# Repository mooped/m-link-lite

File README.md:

# M-Link Lite

M-Link Lite is a receiver for combat robotics based on the ESP8266 microcontroller. It acts as a WiFi access point and can be controlled from a WebSocket.

M-Link Lite hosts a web server with a basic page for controlling a simple combat robot.

Additional files can be uploaded to control more complex robots with up to 6 channels.

The servo pulsewidth data sent to the WebSocket is passed straight through to the outputs to avoid limiting possibilities.

M-Link Lite has a configurable failsafe so if no updates are received for 500ms the outputs will be put into a safe state.

When turned on M-Link will create a WiFi Access Point named m-link-XXXXXX where XXXXXX is a unique set of digits that identifies the device. The device should be labelled with this ID. A single user can connect to this access point and the controller page should be accessible by navigating to http://m-link-XXXXXXX.local or if wildcard DNS is enabled to any url e.g. http://m-link/ .

When connected to the access point the device will always be available at http://192.168.4.1 . If you are having trouble when using the access point from a mobile device, turning off mobile internet so WiFi is the only option may help.

Once configured via the access point you can enter details for your own access point and the device will connect to it from then on.

## Extending M-Link Lite

The default Drive page on the M-Link Lite device provides a single virtual joystick that directly drives the first two channels. It performs no mixing and is designed for a dual ESC with onboard mixing.

If you wish to use all 6 channels or other features you can upload additional files through the File Manager page that make use of these features.

As a starting point it is recommended to download the default 'Drive' page from [main/joystick.html](main/joystick.html), modify it. You can use the File Manager page on the device to upload and test the modified version.

The on-screen Joystick is implemented with [jeromeetienne/virtualjoystick.js](https://github.com/jeromeetienne/virtualjoystick.js) which has its own documentation and examples for adding additional joysticks.

Some examples are provided for implementing [one](examples/joystick.html), [two](examples/two_stick.html), or [three](examples/three_stick.html) on-screen joysticks in the [examples folder](examples) of the project.

The page talks to the M-Link Lite by sending JSON messages over a websocket and the device will send JSON messages back in response.

The code at line 40 of the Drive page sends an initial packet to center all outputs, and it also sends a set of failsafe values which will be applied if a packet is not received for 500 milliseconds. This is intended to avoid the robot going out of control if the user closes their browser, turns of the controlling device, or the connection is otherwise disrupted.

```
        ws.onopen = function() {
          ws.send(
            JSON.stringify(
              {
                servos: [
                  1500,
                  1500,
                  1500,
                  1500,
                  1500,
                  1500
                ],
                failsafes: [
                  1500,
                  1500,
                  1500,
                  1500,
                  1500,
                  1500
                ],
                query: "settings"
              }
            )
          );
        };
```

The default failsafes will stop a brushed ESC that has a reverse feature and center a servo. If you intend to build a robot using non-reversible ESCs or your servo driven mechanisms require a different position on failsafe you will need to update these values.

The values sent in the `servos` and `failsafes` array are the pulse width that will be sent to the servo in microseconds. 1000 microseconds is usually fully left, 2000 microseconds is fully right, and 1500 microseconds is centered. You can send 0 microseconds to stop sending a signal, which will cause many servos to idle, but depending on the servos you will need to be careful with other out of range values which may cause unexpected behaviour and/or damage.

For the `failsafes` array a value of -1 can be set instead of a pulsewidth to hold the channel at its last position when in failsafe.

The code between lines 103 and 124 is responsible for sending updated values to the M-Link Lite 30 times a second. By altering the values to the `servos` array you can make use of all 6 channels.

```
      setInterval(function(){
        const x = Math.round(joystick.deltaX() * 5);
        const y = Math.round(joystick.deltaY() * 5);
        $msg = JSON.stringify({
          servos: [
            parseInt(1500 - y),
            parseInt(1500 + x),
            1500,
            1500,
            1500,
            1500,
          ]
        });
        if ($('#send').val() != $msg || (++counter % keepalive) === 0) {
          $('#send').val($msg);
          ws.send($msg);
        }

        var outputEl  = document.getElementById('result');
        outputEl.innerHTML = $('#wsresponse').val();

      }, 1/30 * 1000);
```

For example you could declare a second VirtualJoystick instance and have it respond to a second area of the screen, and use it to drive 1 or 2 of the extra channels.

These extensions are likely to depend on the intended features of the robot so the system has designed to leave these up to the user while providing maximum flexibility.

For ease of experimentation the default Drive page declares a `mlink` object in the global scope which contains a reference to the WebSocket. You can use this from the browser's Javascript console to send messages manually.

For example, to request the M-Link device send back the current battery voltage reading:

```
mlink.ws.send(JSON.stringify({
  query: "battery"
});
```

## WebSocket API

The WebSocket API expects a JSON message and responds based on the keys contained in the message.

### Sending servo pulsewidths to drive the robot:

For example Ch 1 center/brake, Ch 2 left/reverse, Ch 3 right/forward, Ch 4 center/brake, Ch 5 left/reverse, Ch 6 right/forward

```
{
  servos: [
    1500,
    1000,
    2000,
    1500,
    1000,
    2000
  ]
}
```

The M-Link will read as many channels from the array as it supports and then ignore any additional values. If fewer values are sent than are supported the remaining channels will be left alone.

### Setting Failsafe Positions

For example Ch 1 center/brake, Ch2 left, Ch3 right, Ch4/5/6 hold position

```
{
  failsafes: [
    1500,
    1000,
    2000,
    -1
    -1
    -1
  ]
}
```

The `failsafes` key is handled in the same way as a `servos` key with the exception that -1 is interpreted as hold position.

### Updating settings

```
{
  settings: {
    name: "My Robot",
    ssid: "my-ssid",
    password: "my-password"
  }
}
```

The settings object can contain any or all of the keys `name`, `ssid`, `password` and the settings relating to any keys provided will be updated upon receipt of the packet.

If the SSID or Password for the WiFi are changed the settings will be saved immediately but the device must be rebooted before they will take effect.

The SSID and Password fields refer to an external Access Point the device will try to connect to. The details for the M-Link's Access Point are fixed and cannot be changed.

### Resetting Settings

```
{
  reset_settings: "sgnittes_teser"
}
```

The `reset_settings` key will cause a reset of all settings to factory defaults as soon as it is received, so long as the value is the string `"reset_settings"` backwards to prevent accidental resets.

### Rebooting

```
{
  reboot: "toober"
}
```

The `reboot` key will cause an immediate reboot of the device so long as the value is the string `"reboot"` backwards, to prevent accidental reboots.

This can be used after updating settings to apply any that require a reboot to take effect.

### Query

The query key can be used to read various values back from the M-Link.

```
{
  query: "battery"
}
```

The device will respond to a `battery` query with an object containing the value read on the ADC which may be connected to an external battery of the 5v rail of the servo connectors depending on the device and how it is wired.

```
{
  query: "failsafes"
}
```

The device will respond to a `failsafes` query with the current failsafe values.

```
{
  query: "settings"
}
```

The device will respond to a `settings` query with an object containing the current settings.

## Safety

M-Link Lite is designed as a simple device to make it easy to get started and because of this it has been designed to be simple and robust at the expense of some security features.

To avoid users locking themselves out of the device its Access Point has a fixed password, and when connected to a shared Access Point there is no authentication to prevent other users from taking control of the device. For this reason we do not recommend using this device for any robot with spinning weapons or any other weapons that would be dangerous if activated unexpectedly.

## Building The Project

This project is based on the ESP8266 FreeRTOS SDK, which is the ESP8266 equivalent of the ESP32's ESP-IDF project.

You can find instructions for installing and setting this up in their [Getting Started Guide](https://docs.espressif.com/projects/esp8266-rtos-sdk/en/latest/get-started/index.html).

This project uses a version of the ESP8266 FreeRTOS SDK that I modified to include the ESP32 version's web server. You will need to check out [my ESP8266_RTOS_SDK_ESP32TTTPD project](https://github.com/mooped/ESP8266_RTOS_SDK_ESP32HTTPD) instead of the official version.

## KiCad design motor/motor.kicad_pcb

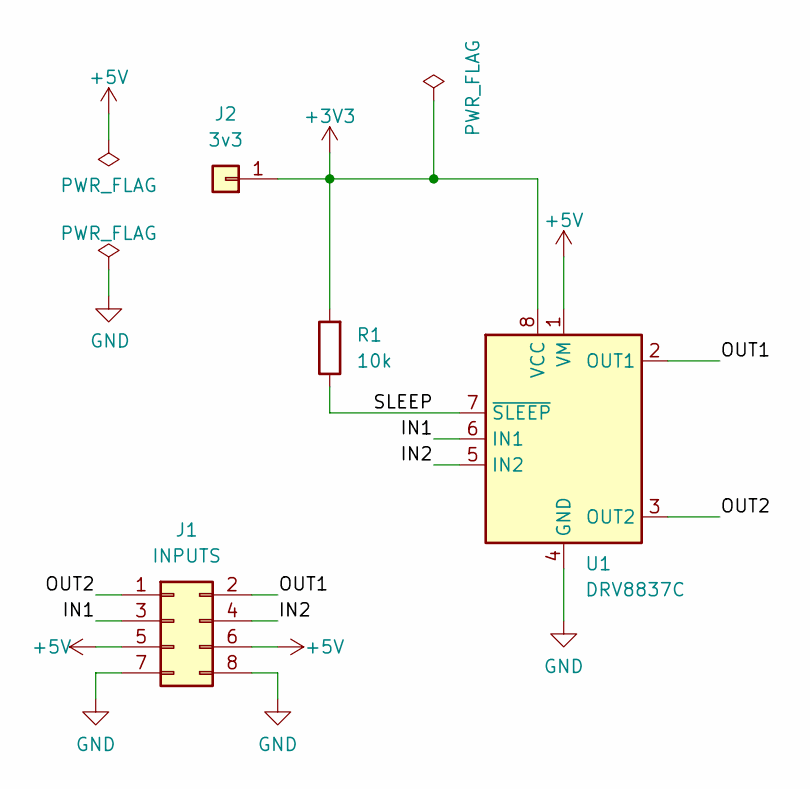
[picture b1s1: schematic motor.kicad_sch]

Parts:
J1: INPUTS; PinHeader_2x04_P2.54mm_Vertical
J2: 3v3; PinHeader_1x01_P2.54mm_Vertical
R1: 10k; R_0603_1608Metric
U1: DRV8837C; WSON-8-1EP_2x2mm_P0.5mm_EP0.9x1.6mm

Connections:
+3V3: J2.1, R1.2, U1.8 (VCC)
+5V: J1.5, J1.6, U1.1 (VM)
/IN1: J1.3, U1.6 (IN1)
/IN2: J1.4, U1.5 (IN2)
/OUT1: J1.2, U1.2 (OUT1)
/OUT2: J1.1, U1.3 (OUT2)
/SLEEP: R1.1, U1.7 (~SLEEP)
GND: J1.7, J1.8, U1.4 (GND), U1.9 (GND)

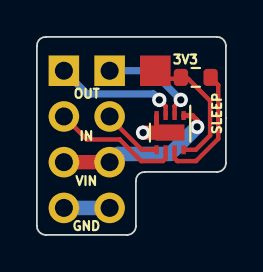
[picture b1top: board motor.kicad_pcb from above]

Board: 2 copper layers, 10.5 x 11.0 mm, 4 parts (0 on the bottom side), 8 nets.

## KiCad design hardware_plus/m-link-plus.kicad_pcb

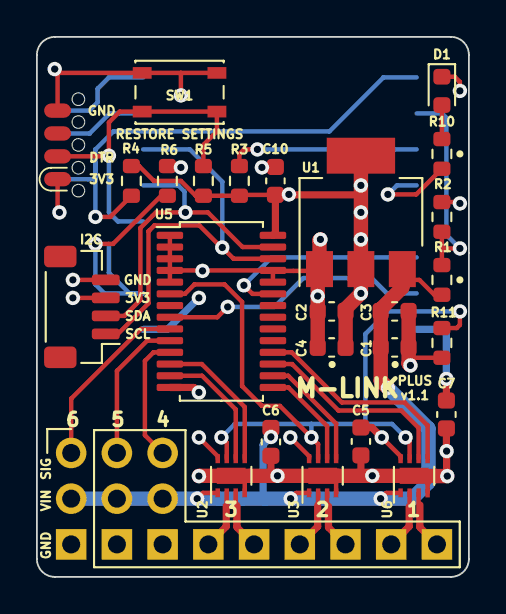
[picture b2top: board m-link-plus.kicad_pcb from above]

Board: 4 copper layers, 24.0 x 30.0 mm, 27 parts (1 on the bottom side), 32 nets.

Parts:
C1, C4: 1u; C_0603_1608Metric
C2, C3, C5, C6, C7, C10: 100n; C_0603_1608Metric
D1: STATUS; LED_0603_1608Metric
J3: SIG; ServoHeader_3x06_P2.54mm_Vertical
J4: PROGRAM; SOIC_clipProgSmall
J5: I2C; JST_SH_BM04B-SRSS-TB_1x04-1MP_P1.00mm_Vertical
R1: 33k; R_0603_1608Metric
R2, R3, R4, R5, R6, R11: 10k; R_0603_1608Metric
R10: 100; R_0603_1608Metric
SW1: RESTORE SETTINGS; SW_SPST_PTS810
U1: AP1117-33; SOT-223-3_TabPin2
U2, U3, U6: DRV8837C; WSON-8-1EP_2x2mm_P0.5mm_EP0.9x1.6mm
U4: ESP-12F; ESP-12E
U5: PCA9685PW; TSSOP-28_4.4x9.7mm_P0.65mm

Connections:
+3V3: C2.1, C4.1, C5.1, C7.1, C10.1, J4.1, J5.3, R3.1, R4.1, R5.1, U1.2 (VO), U2.8 (VCC), U3.8 (VCC), U4.8 (VCC), U5.28 (VDD), U6.8 (VCC)
+5V: C1.1, C3.1, C6.1, J3.2, J3.5, J3.8, R1.1, U1.3 (VI), U2.1 (VM), U3.1 (VM), U6.1 (VM)
/ADC: R1.2, R2.1, U4.2 (ADC)
/CH1: J3.1, U5.9 (LED3)
/CH2: J3.4, U5.10 (LED4)
/CH3: J3.7, U5.11 (LED5)
/CH4: U2.6 (IN1), U5.13 (LED7)
/CH5: U2.5 (IN2), U5.12 (LED6)
/CH6: U3.6 (IN1), U5.15 (LED8)
/CH7: U3.5 (IN2), U5.16 (LED9)
/CH8: U5.17 (LED10), U6.6 (IN1)
/CH9: U5.18 (LED11), U6.5 (IN2)
/DTR: J4.2, R5.2, SW1.2, U4.18 (GPIO0)
/EN: R3.2, U4.3 (EN)
/ENABLE: U4.6 (GPIO12), U5.23 (~OE)
/FEEDBACK: U4.7 (GPIO13), U5.8 (LED2)
/LED1: R10.1, U4.4 (GPIO16)
/M1A: J3.10, U2.2 (OUT1)
/M1B: J3.11, U2.3 (OUT2)
/M2A: J3.12, U3.2 (OUT1)
/M2B: J3.13, U3.3 (OUT2)
/M3A: J3.14, U6.2 (OUT1)
/M3B: J3.15, U6.3 (OUT2)
/MTDI: R6.1, U4.16 (GPIO15)
/RESET: J4.8, R4.2, U4.1 (~RST)
/RX: J4.5, U4.22 (GPIO1/TXD)
/SCL: J5.1, U4.20 (GPIO5), U5.26 (SCL)
/SDA: J5.2, U4.19 (GPIO4), U5.27 (SDA)
/SLEEP: R11.2, U2.7 (~SLEEP), U3.7 (~SLEEP), U5.6 (LED0), U6.7 (~SLEEP)
/TX: J4.6, U4.21 (GPIO3/RXD)
GND: C1.2, C2.2, C3.2, C4.2, C5.2, C6.2, C7.2, C10.2, D1.1 (K), J3.3, J3.6, J3.9, J4.4, J5.4, R2.2, R6.2, R11.1, SW1.1, U1.1 (GND), U2.4 (GND), U2.9 (GND), U3.4 (GND), U3.9 (GND), U4.15 (GND), U5.1 (A0), U5.2 (A1), U5.3 (A2), U5.4 (A3), U5.5 (A4), U5.14 (VSS), U5.24 (A5), U5.25 (EXTCLK), U6.4 (GND), U6.9 (GND)
unnamed: D1.2 (A), R10.2

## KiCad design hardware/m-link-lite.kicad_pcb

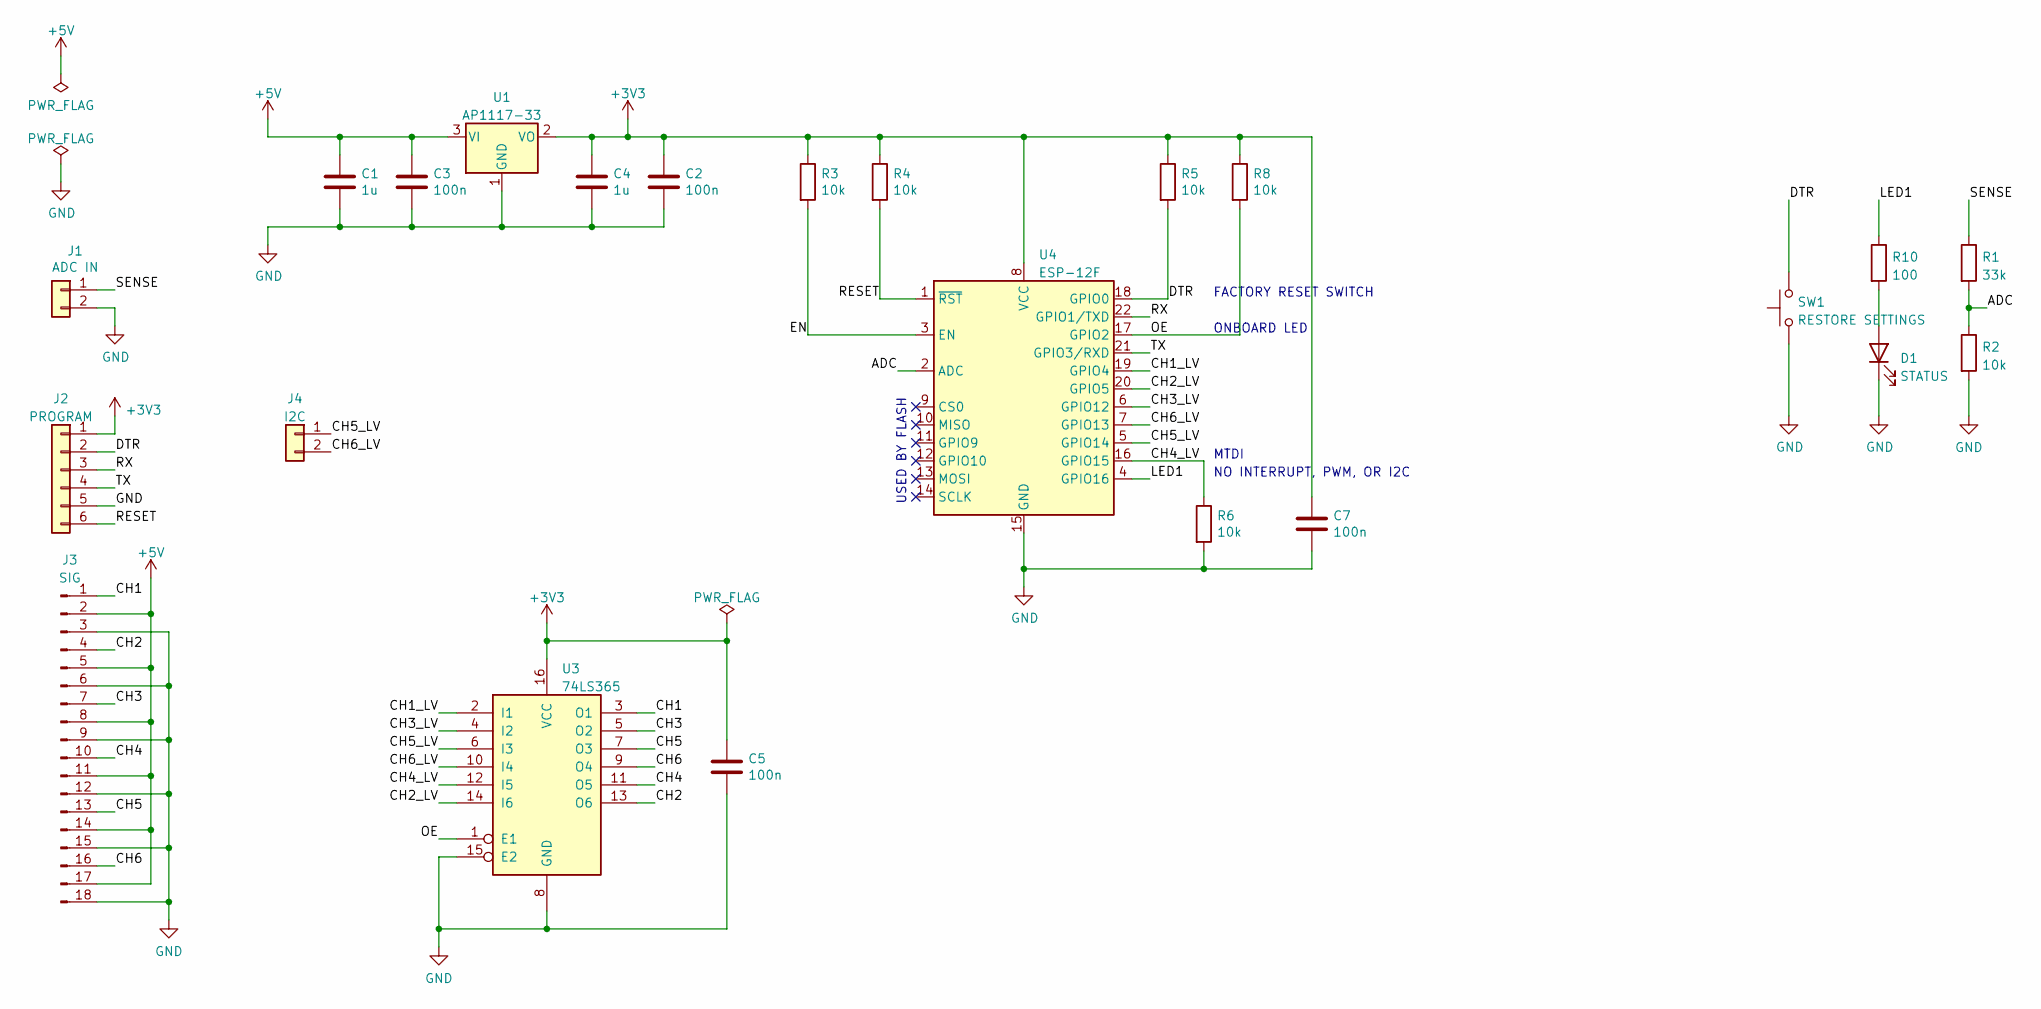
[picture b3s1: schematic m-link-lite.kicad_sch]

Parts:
C1, C4: 1u; C_0603_1608Metric
C2, C3, C5, C7: 100n; C_0603_1608Metric
D1: STATUS; LED_0603_1608Metric
J1: ADC IN; PinHeader_1x02_P2.54mm_Vertical
J2: PROGRAM; PinHeader_1x06_P2.54mm_Vertical
J3: SIG; ServoHeader_3x06_P2.54mm_Vertical
J4: I2C
R1: 33k; R_0603_1608Metric
R2, R3, R4, R5, R6, R8: 10k; R_0603_1608Metric
R10: 100; R_0603_1608Metric
SW1: RESTORE SETTINGS; SW_SPST_PTS810
U1: AP1117-33; SOT-223-3_TabPin2
U3: 74LS365; SO-16_3.9x9.9mm_P1.27mm
U4: ESP-12F; ESP-12E

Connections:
+3V3: C2.1, C4.1, C5.1, C7.1, J2.1, R3.1, R4.1, R5.1, R8.1, U1.2 (VO), U3.16 (VCC), U4.8 (VCC)
+5V: C1.1, C3.1, J3.2, J3.5, J3.8, J3.11, J3.14, J3.17, U1.3 (VI)
/ADC: R1.2, R2.1, U4.2 (ADC)
/CH1: J3.1, U3.3 (O1)
/CH1_LV: U3.2 (I1), U4.19 (GPIO4)
/CH2: J3.4, U3.13 (O6)
/CH2_LV: U3.14 (I6), U4.20 (GPIO5)
/CH3: J3.7, U3.5 (O2)
/CH3_LV: U3.4 (I2), U4.6 (GPIO12)
/CH4: J3.10, U3.11 (O5)
/CH4_LV: R6.1, U3.12 (I5), U4.16 (GPIO15)
/CH5: J3.13, U3.7 (O3)
/CH5_LV: J4.1, U3.6 (I3), U4.5 (GPIO14)
/CH6: J3.16, U3.9 (O4)
/CH6_LV: J4.2, U3.10 (I4), U4.7 (GPIO13)
/DTR: J2.2, R5.2, SW1.2, U4.18 (GPIO0)
/EN: R3.2, U4.3 (EN)
/LED1: R10.1, U4.4 (GPIO16)
/OE: R8.2, U3.1 (E1), U4.17 (GPIO2)
/RESET: J2.6, R4.2, U4.1 (~RST)
/RX: J2.3, U4.22 (GPIO1/TXD)
/SENSE: J1.1, R1.1
/TX: J2.4, U4.21 (GPIO3/RXD)
GND: C1.2, C2.2, C3.2, C4.2, C5.2, C7.2, D1.1 (K), J1.2, J2.5, J3.3, J3.6, J3.9, J3.12, J3.15, J3.18, R2.2, R6.2, SW1.1, U1.1 (GND), U3.8 (GND), U3.15 (E2), U4.15 (GND)
unnamed: D1.2 (A), R10.2

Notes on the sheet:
FACTORY RESET SWITCH
NO INTERRUPT, PWM, OR I2C
USED BY FLASH
ONBOARD LED
MTDI

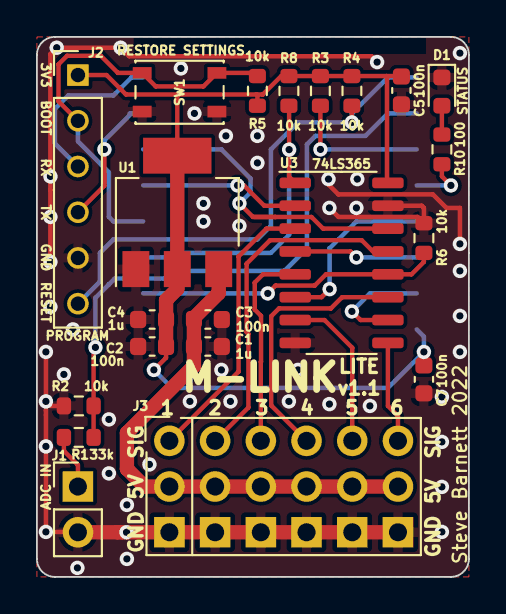
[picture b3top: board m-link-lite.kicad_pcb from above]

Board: 2 copper layers, 24.0 x 30.0 mm, 22 parts (1 on the bottom side), 25 nets.

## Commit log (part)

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2022-03-28 Initial commit - interface for PWM, and start of an interface for ESPNOW.
2022-03-29 Readme with flow charts for the TX and RX. Tidy up ESPNOW code to keep it self contained.
2022-03-31 Rework to extract recv and send callbacks.
2022-04-02 Refactoring to support combined RX/TX source. PWM for TX LEDS. Initial work on PPM for the TX.
2022-04-03 Rework directory structure. Low resolution PPM decode using hw_timer interrupt to increment a counter every 50us.
2022-04-03 Update readme. Working transmission of control data (currently broadcast only).
2022-04-03 Implement brakes on channels 6, 7, and 8.
2022-04-03 Document PPM channel assignments.
2022-04-03 Begin work on unicast after RX/TX handshake.
2022-04-04 Make sure incoming control data and MAC addresses are sent between tasks via queue.
2022-04-05 Action transport send and add_peer actions on the ESPNOW task. General tidy up. Fix use after free of send_param's buffer after any transport_send!
2022-04-05 Further pruning of unused ESPNOW code. Add an externally accessible transport_deinit method that operates via a queue.
2022-04-07 Add a timer to the RX to determine when to enter bind mode.
2022-04-07 Ignore messages received before control task queue is allocated. Remove receiver bind mode for now to avoid messing around with writing to Flash.
2022-04-07 Implement failsafe.
2022-04-09 Initialise rx/tx task queues before the WiFi task to handle data received before the rx task is created. Load bound TX MAC address from NVS on startup.
2022-04-09 Reimplement bind mode. Move LED control to its own driver using a software timer to reduce PWM cost.
2022-04-09 Rework LED driver with data driven config so the code can be common between TX and RX.
2022-04-09 LED driver special case for solid on/off to save using timers. Rework RX LED management. Ignore control updates during binding.
2022-04-10 Implement TX LED states. Create a driver to read battery voltage via ADC.
2022-04-10 Implement basic signal quality indicator by tracking sequence numbers.
2022-04-10 Implement RX side of telemetry.
2022-04-10 TX telemetry receiver task. OLED bring up (Hello World).
2022-04-10 Basic telemetry layout. Tweak font to add uppercase letters as placeholders for lower case.
2022-04-10 Add battery and antenna glyphs.
2022-04-10 Rework telemetry display. 1 line for RX, 1 line for TX, 1 line for RX mac, 1 spare line.
2022-04-13 Disable motors as early as possible. Optimise and remove logs. Remove unused tw-pwm module.
2022-04-13 Rename tx-ppm module to ppm.
2022-04-13 Rename rx-pwm module to motor (pwm clashes with ESP8266 pwm driver).
2022-04-13 PPM optimisation and smoothing.
2022-04-13 Rework PPM interpretation on receiver. Add deadzone and change brake controls to select between brake or coast in deadzone. Enable PPM debug output driven by bind switch.
2022-04-15 Remove smoothing but improve PPM decode quality by ignoring rollover and blocking non-essential tasks during the critical part of the frame.
2022-04-20 Start work on firmware for PPM offload.
2022-04-21 Working PPM tracking with 1uS resolution.
2022-04-21 Refactor to double buffer PPM data. Add usitwislave submodule to track where the files from that repo came from.
2022-04-22 Calculate and update latency when sending data.
2022-04-22 Implement support for PPM offload helper with fallback to onboard PPM capture.
2022-04-23 PPM offload fallback improvements.
2022-04-23 Rework PPM capture by actively timing the gaps for error detection.
2022-04-27 Fix PWM period to allow driving the motors at full power.
2022-07-07 Drive servo outputs and remove m-link code to be replaced with WiFi.
2022-07-12 Working webserver in STA mode for M-Link Lite.
2022-07-13 Add .gitignore.
2022-07-15 Generate pulsewidths in Javascript and pass straight to servo driver.
2022-07-15 Update .gitignore.
2022-07-15 Add script to build and flash SPIFFS image.
2022-07-15 Add mkspiffs submodule and fix scripts.
2022-07-16 Fix memory leak from not freeing cJSON objects.
2022-07-16 Implement user configurable failsafe.
2022-07-16 Tweak LED states for failsafe.
2022-07-16 Rework file handling so essential pages are baked in to Flash. File manager is at /files/ and handles SPIFFS file management.
2022-07-16 Update comment.
2022-07-16 Serve jQuery. Add support for APSTA mode.
2022-07-16 Rework APSTA config. Separate out hostname generation so we can use it for SSID and hostname.
2022-07-17 Captive DNS server. Work on a settings mechanism for managing APSTA mode.
2022-07-17 Update README.md to match this version of the project.
2022-07-17 Tidy up and remove unused source files. Add schematics and PCB files for v1.0 board.
2022-07-17 Update README.md.
2022-07-17 Rework settings UI to work via websockets. Implement query interface for settings, failsafes, battery telemetry.
2022-07-17 Send failsafes and battery voltage as strings to workaround cJSON issues.
2022-07-17 Add style.css (baked in with override).
2022-07-17 Add virtualjoystick.js submodule.
2022-07-17 More UI tidying. Toggle menu. Add more mime types.
2022-07-17 Tidy up AP only mode.
2022-07-17 Rework and fix APSTA failure handling.
2022-07-17 Fallback to AP only if no STA SSID is configured. Allow rebooting from Settings page. Show AP SSID on settings page (read only).
2022-07-18 Move captDns initialisation into dns.c
2022-07-18 Remove spurious logging from settings.html.
2022-07-18 Add a menu on the index page and move the joystick to /drive.
2022-07-22 Add extra documentation to README.md.
2022-07-22 Add examples folder (and copies of the files needed to run them in a local browser).
2022-07-23 Support for generating a (better than 'password') password from MAC address.
2022-07-23 Start implementing a unique password mechanism.
2022-07-23 Add link to modified RTOS SDK in the readme.
2022-07-23 Implement password generation.
2022-07-24 Update the password generator to match onboard behaviour.
2022-07-24 Password improvements.
2022-07-24 Rework v1.2 layout.
2022-07-25 Rotate regulator 180.
2022-07-25 Tidy up.
2022-07-27 Initial pass on a thin JS wrapper for the websocket.
2022-07-31 First pass at (partially) implementing m-link.js and converting joystick.html to use it.
2022-07-31 Implement a promise based mechanism to return the response for a specific call.
2022-08-01 Streamline initialisation. Extract and return only the relevant values from get methods.
2022-08-02 Use m-link.js in all examples.
2022-08-02 Simple servo tester example. Update m-link.js to allow querying the number of channels (for forwards compatibility).
2022-08-07 Initial layout for arena controller.
2022-08-07 Working arena clock (without M-Link integration or sound effects).
2022-08-08 Reference Orbitron font via Google Fonts.
2022-08-08 Fit to screen width if possible and make the vertical spacing more flexible.
2022-08-13 Default WebSocket connection to location.host otherwise use the host hash argument.
2022-08-13 Implement defaultHost logic in m-link.js.
2022-08-13 Extract countdown logic into a reusable class with event support.
2022-08-13 Support for triggering servos at half time and sound effects (if provided).
2022-08-13 Embed m-link.js into Flash and update embedded scripts. Streamline embedded file serving. Tweak arena.html to avoid hitting the failsafe.
2022-08-16 onmessage argument is an object not a string, so don't JSON.parse it.
2022-08-16 Flipper example with a button.
2022-08-16 Tweak flipper button dimensions.
2022-09-25 Layout tweaks.
2022-09-28 Plot v1.1.
2022-11-07 Hardware v1.1 as manufactured.
2022-11-07 Add stencil DXFs.
2022-11-12 Implement button handler and support settings reset on 10 second hold.
2022-11-14 Add 'plus' version of the hardware with 3 built in motor drivers and 3 servo outputs.
2022-11-14 Rework M-Link Plus by swapping the PCA9865 and the regulator.
2022-11-16 Add resistors back to GPIO2 and GPIO15.
2022-11-21 Plot M-Link Plus v1.0
2022-11-21 Improve ground plane.
2022-11-28 M-Link plus gerbers and stencil files.
2022-12-14 Tidy up fab layer.
2022-12-16 Implement basic support for the Plus version of the hardware.
2022-12-21 Increase PWM frequency to 483Hz for motors and actively disable after a single cycle to drive the servos. Really needs feedback to an IO to sync with the PCA9685 clock to avoid missing servo PWM cycl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
2022-12-28 Implement feedback path from PCA9865 to an ESP8266 input for timing.
2022-12-30 Remove DOCTYPE from example HTML since the joystick requires quirks mode.
2022-12-30 Remove DOCTYPE from examples as the joystick requires quirks mode.
2023-03-14 Begin rework to add an optional fourth channel.
2023-03-20 Remove unnecessary resistors and begin improving layout.
2023-03-22 Move feedback pin on the pca9685 to be adjacent to the servos.
2023-03-27 Backport servo output support from M-Link base firmware. Add interactive HTML BOM for both boards.
2023-03-27 Tidy up plus layout. Add plus HTML BOM.
2023-03-28 Version 1.1 ready for manufacture.
2023-03-28 Add a daughterboard with an extra DRV8837 to drive a fourth motor.
2023-05-02 Implement settings for the local AP SSID/hostname and password. Support default password generated from MAC address or a fixed string.
2023-05-05 Set mDNS hostname from settings.
2023-05-05 WIP joystick implementation with nipplejs.
2023-05-05 Implement an early out when a packet is only updating servo outputs.
2023-05-05 Support for M-Link Plus v1.1 board.
2023-05-05 Disable servo output as it is causing huge latency.
2023-05-06 Fall back to cheaper PWM output from the 'servo' channels. Mixing for steering.
2023-06-29 WIP layout editor.
2023-08-30 Static form for panel editor.
2023-09-03 Rework edit.html with a grid based layout.
2023-09-03 Add name attributes for easy serialisation with $(...).serialize().
2023-09-03 First pass at parsing the grid layout.
2023-09-03 Consistency pass on form elements.
2023-09-03 Implement foreground and background colours. Move header back to the top.
2023-09-03 Media queries to stack the panels vertically on narrow screens.
2023-09-03 Remove the concept of in-line editing from grid.js.
2023-09-03 Implement the button application.
2023-09-03 Label support. Test alternate form layout.
2023-09-04 Move Idle/Active controls into input range (-1 to 1). Duplicate new style inputs to all panels. Fix Panel 6 background colour inputs.
2023-09-04 Implement joystick and button readback. Consistent button padding.
2023-09-04 Implement mixing. Handle joystick release. Send data to the controller.
2023-09-04 Use .no-edit class to toggle editor layout. Add Layout Editor to the menu. Replace joystick.html with what was edit.html.
2023-09-04 Hook up mixing preview outputs.
2023-09-05 Implement save/load/preset selection UI elements.
2023-09-06 Add pointer events.
2023-09-06 Setup built in presets.
2023-09-13 Serve grid.js. Begin implementing presets (client side only currently).
2023-09-24 Implement save and load using the existing filesystem APIs. Fix Two Stick preset.
2023-10-12 Unify the codebase with config macros for boards and features.
2023-10-17 Initial work on hexapod support. Cleanup.
2023-10-22 Implement low level support for a hexapod with 19 channels (18 for legs, one auxiliary). This can use two PCA9685 breakout boards or one breakout and an M-Link Plus board (16+3).
2023-10-22 WIP leg solver, with targets translated by the same amount per leg.
2023-10-23 Log and ignore NaNs. Tweak stance and smoothing.
2023-10-23 Solver improvements.
2023-10-23 More compact default stance, and cumulative stance modification. Fix tibia angle.
2023-10-23 Very basic and hacky alternating tripod gait.
2023-10-23 Hacky rotation and scaling of stride height by stroke length, up to a limit.
2023-10-23 Serve hexapod files from the device.
2023-10-24 Clamp leg target distance to avoid unreachable regions.
2023-10-24 Tweak gait for constant ride height.
2023-10-24 Tweak trims. Longer default stance front to back.
2023-10-24 New startup sequence. Implement multiple states.
2023-10-25 Offset servo outputs on the local PCA9685 to support M-Link boards.
2023-10-26 Set the enable pin low in the hexapod servo driver.
